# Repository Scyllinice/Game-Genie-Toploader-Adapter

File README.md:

# Game Genie Toploader Adapter

<p xmlns:cc="http://creativecommons.org/ns#" >This work by <span property="cc:attributionName">Scyllinice</span> is licensed under <a href="https://creativecommons.org/licenses/by-nc/4.0/?ref=chooser-v1" target="_blank" rel="license noopener noreferrer" style="display:inline-block;">Creative Commons Attribution-NonCommercial 4.0 International</a></p>

This is a adapter/riser PCB for using an original Game Genie on your top loading NES. It also works for clone NES systems that load directly from the cart instead of using emulation (a Retron 5, for example, will not work).

The only component needed to build this PCB into a functioning unit would be a 2.54mm pitch 2x36 pin (72 pin total) edge connector. You can search **5530843-8** for a part number as well.

I have had success using the following edge connectors:

* [Edge connector 1](https://www.aliexpress.us/item/3256802817047324.html)
* [Edge connector 2](https://www.aliexpress.us/item/2251832843397196.html)
* [DigiKey](https://www.digikey.com/en/products/detail/te-connectivity-amp-connectors/5530843-8/770547)

When soldering the edge connector to the top of the board, you will need to bend in the pins a bit as the board is only 1.2mm thick to match the original thickness of a NES retail cartridge. This helps preserve the NES cartridge connector. 

For longevity, it is recommended to use an ENIG finish with gold fingers. HASL (or Lead Free HASL) will still work, but it's more fragile and can fail over time.

[JLCPCB](https://jlcpcb.com/) is generally better priced for ENIG gold fingers than PCBWay. As the time of this writing, you can get 5 of these boards for about $20 US at JLCPCB.

## 3D printed enclosure — [`mech/`](mech/README.md)

A two-part shell, **106.1 × 16.8 × 58.4 mm**, held together by two M2 screws through
the board's own mounting holes. Prints without supports; `mech/front.stl` and
`mech/back.stl` are ready to slice.

## The KiCad project lives in [`pcb/`](pcb/README.md)

The board is now **generated from source rather than drawn**: a 72-pin pinout table and
a set of measured dimensions, from which the footprints, symbols, schematic, board,
copper and fab outputs are all produced by `make rebuild`.

```
cd pcb
make            check what is committed — DRC, ERC, card-edge rules, and the
                comparison against the board that was released
make rebuild    regenerate everything from the two source tables
make fab        gerbers, drill, position file, BOM
```

Regenerating wants the pinned toolchain — `./dc bash -c "cd pcb && make rebuild"` runs
it in a container with KiCad 10 and OpenSCAD, which is what the committed files were
built with. See [`.devcontainer/`](.devcontainer/README.md). Checking works with
whatever KiCad you have.

It is the same board. The hand-drawn files this project shipped with are frozen in
[`pcb/reference/`](pcb/reference/README.md), and every run subtracts the generated
board from them — 144 pads, 72 nets, 14 outline corners, both holes, all three silk
texts, to within 1 µm. Nothing about the physical board, the pinout or the fab package
has changed.

What the rebuild adds: a schematic that passes ERC (the drawn one reports 54 direction
conflicts, because one symbol was used for both ends of a pass-through), card-edge
checks KiCad's DRC does not have (finger pitch, front/back registration, the bevel
zone, the contact wipe path), ENIG and the 1.2 mm stackup declared in the gerber job
file rather than only in this README, and a rebuild that is byte-identical run to run.

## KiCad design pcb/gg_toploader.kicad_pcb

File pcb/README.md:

# pcb/ — the board

The Game Genie Toploader Adapter, generated from source instead of drawn. Two Python
tables describe the board — a 72-pin pinout and a set of measured dimensions — and
everything else here is produced from them: both footprints, both schematic symbols,
the schematic, the board, the copper, the project rules and the fab outputs.

**This is the project of record.** It replaced the hand-drawn files that used to sit
in the repository root, which are frozen in [`reference/`](reference/README.md) — not
as an archive, but because the check below reads them. The generated board is
subtracted from the released one on every run:

```
  PASS  outline  — 14 corners vs 14
  PASS  pad count  — 144 pads
  PASS  pad positions  — 144 pads within 0.001 mm
  PASS  pad sizes
  PASS  pad layers
  PASS  pad nets  — 72 nets
  PASS  net membership  — 72 nets
  PASS  1:1 pass-through  — 72/72 nets join J1 pin N to J2 pin N
  PASS  mounting holes  — (100.914, 79.451) d2.1, (171.348, 79.451) d2.1
  PASS  silk texts  — 3 texts

  The rebuild is geometrically and electrically identical to the released board.
```

## Running it

```
make            check what is here — DRC, ERC, card-edge rules, byte-canonical
                form, and the comparison above. Regenerates nothing.
make rebuild    the whole pipeline, pin table to routed board (FORCE=1 to overwrite
                a board that already carries routing)
make compare    just the equivalence proof
make fab        gerbers, drill, position file, BOM
make render     top and bottom PNGs, and the repository README's image
```

Needs KiCad 9 on the host — `kicad-cli` and the `pcbnew` Python module, both of which
Debian/Ubuntu's `kicad` package installs. No container. The generated files are KiCad
9 format while the released ones are KiCad 8, which is exactly why the comparison
loads both through pcbnew instead of diffing text.

## What the board is

A passive riser. 72 gold fingers go into a top-loading NES; a 2×36 2.54 mm card-edge
connector soldered to the top takes the Game Genie. Pin N to pin N, seventy-two times,
no components. The one and only complication:

**The two ends are on different pitches.** The console's cartridge slot is 2.50 mm and
the connector part is made in 2.54 mm, so every conductor has to shift sideways
between the two fields — 1.67 mm at one end of the board, 3.07 mm at the other. That
shift is the entire routing problem, and it is why the corridor between the two pad
fields is full of parallel diagonal jogs.

**Two mounting holes sit in that corridor** and four conductors cannot clear them in
either pad column, so they jog twice: once early, hold a safe X past the hole, then
finish the move in the 2.75 mm window between the hole and J1's pads. The released
board does this by hand. `route.py` derives it, and refuses to write a board where it
does not fit.

## The pipeline

```
lib/pinout.py      72 pins: nesdev name, this board's net label, symbol pin, direction
lib/geometry.py    the measured board: outline, both pad fields, holes, silk, rules
      |
      |  gen_footprints.py  -> lib/gg_adapter.pretty/   (2 footprints, 144 pads)
      |  gen_symbol.py      -> lib/gg_adapter.kicad_sym (2 symbols, mirrored)
      |  gen_schematic.py   -> gg_toploader.kicad_sch   (2 symbols, 144 labels)
      |  gen_board.py       -> gg_toploader.kicad_pcb   (placed + netted, unrouted)
      |  route.py           -> + 220 track segments, clearance-audited
      |  canonicalize.py    -> byte-reproducible (content-derived UUIDs, sorted items)
      |  gen_project.py     -> gg_toploader.kicad_pro + both lib tables
      v
   checks: kicad-cli drc (0/0) · kicad-cli erc (0) · check_fingers.py ·
           verify_rules.py · compare_original.py
```

`gen_project.py` runs **last**. `pcbnew.SaveBoard()` rewrites the sibling `.kicad_pro`
and resets the net classes to KiCad's stock defaults; `verify_rules.py` is what catches
it when that ordering slips.

## What the rebuild adds

Everything below is a difference from the released project, and each one is deliberate:

| | released | rebuild |
|---|---|---|
| ERC | 54 violations | **0** |
| symbols | one symbol used twice, all 72 nets output-to-output | two symbols, directions mirrored console↔Game Genie |
| symbol source | `doragasu:NES-CART`, a CERN-OHL-S library | generated from the nesdev wiki pin table |
| stackup finish | `None` | `ENIG` — reaches the fab in the gerber job file instead of living in a README |
| card-edge checks | none | pitch, registration, bevel zone, wipe path, mask, edge clearance |
| keepouts | none | rule areas over the bevel/wipe zone and the top edge |
| fab instructions | in this README | `fab/FABNOTES.txt`, in the zip with the gerbers |
| regeneration | n/a | byte-identical across runs |

DRC was already clean on the released board, and stays clean here: 0 violations,
0 unconnected.

## The card edge, and the check KiCad does not run

**DRC's copper-to-edge test does not look at pads.** Measured here: set
`min_copper_edge_clearance` to 5 mm — far enough that all 144 pads are inside it — and
the violation list comes back with 16 items, every one a *track*. Not one pad, at any
setting. On most boards that is a curiosity. On a card edge the pads are the thing
nearest the milled edge, so the check that matters is the one that does not run.

Two things cover it between them:

**Rule areas** (`gen_board.py`) over the bevel/wipe zone at the insertion edge and over
the top edge. Nothing may be *routed* into either band. The insertion-edge one is there
twice over: a 45° gold-finger bevel takes ~0.6 mm off the top surface, so copper inside
it is copper the mill cuts through — and the console's contacts sweep that same strip
on every insertion, so a track crossing it shorts to each contact as it passes. They
are rule areas, not copper: the gerbers are byte-identical with and without them,
verified.

**`check_fingers.py`** measures what a keepout cannot enforce, because keepouts permit
pads. It reports the closest pad to any edge — J1.36 at **0.372 mm** — and fails only
below 0.20 mm, the floor a fab can actually hold on a routed edge. All 72 J1 pads sit
inside this project's own 0.5 mm rule, at 0.468 mm from the top edge. That is
as-released and as-fabricated: the connector land has to be where the connector is.
Noted every run, not changed.

**The bevel itself is not board geometry** — it is a process the fab applies, and
there is no field in any gerber that asks for it. That instruction now ships as
`fab/FABNOTES.txt` inside the fab package rather than living in a README, because a
fab that is not told sends back square-edged contacts that chew the console connector.

## Things worth knowing about this board

* **1.2 mm, not 1.6 mm.** Cartridge thickness. The stackup declares 1.11 mm core plus
  copper and mask to reach it, and the gerber job carries the number.
* **The finger setback is 0.62 mm** and a 45° gold-finger bevel on a 1.2 mm board
  reaches about 0.6 mm. That is a **0.02 mm margin** — `check_fingers.py` prints it
  every run because it is the kind of number you want to have seen before ordering.
* **Pins 1 and 72 are both GND and are NOT joined here.** They are separate nets
  (`CPU-GND`, `CIC-GND`) and meet in the console. `pinout.py` asserts it stays that
  way; bridging them would be a change of circuit, not a cleanup.
* **PPU A11 and A10 really are swapped** at pins 62/63. Wiki and released board agree.
* **CIRAM A10 and CIRAM /CE are driven by the cartridge**, so they are the two signals
  whose direction runs Game-Genie-to-console. The released symbol has them as inputs;
  this is the only place the rebuild's pin table disagrees with it, and it changes
  nothing but ERC.

## Traps this cost, written down where they happened

* `.kicad_pcb` writes text size in the **opposite order** to `VECTOR2I`, and
  `SetBold()` **recomputes thickness**, so it has to be called before setting it.
  Between them, the long silk text came out short, fat and off the edge.
* A schematic's inlined `lib_symbols` copy is **library-qualified**, but its
  `_0_0`/`_1_1` sub-symbols are **not**. Get it wrong and KiCad rejects the whole file
  with "Failed to load schematic" and no line number.
* That inlined copy is compared **field by field** against the library. A description
  that differs by one word is an ERC warning, which is why both files build their
  symbols from one table.
* The escape columns beside a mounting hole are `hx ± R`, and `(hx - R) - hx` is not
  exactly `-R` in floating point, so an exact-fit candidate rejects itself. Two
  conductors failed to route over 1e-13 mm.

## Files

| file | what it makes |
|---|---|
| `lib/pinout.py` | the 72-pin table — run it to print the pinout |
| `lib/geometry.py` | measured geometry — run it to print the dimensions |
| `gen_footprints.py` | `lib/gg_adapter.pretty/` — the fingers and the connector land |
| `gen_symbol.py` | `lib/gg_adapter.kicad_sym` — two direction-mirrored symbols |
| `gen_schematic.py` | the schematic: two symbols, 144 labels, no wires |
| `gen_board.py` | the board: outline, placement, holes, silk, 72 nets |
| `route.py` | the copper, in closed form, clearance-audited before it is written |
| `canonicalize.py` | content-derived UUIDs so a no-op rebuild is a no-op diff |
| `gen_project.py` | net classes, design rules, both library tables |
| `gen_bom.py` | the BOM — one line, plus the fab notes that matter |
| `gen_render.py` | the two renders, and the repository README's image |
| `compare_original.py` | the equivalence proof against the released board |
| `check_fingers.py` | card-edge checks KiCad's DRC does not have |
| `verify_rules.py` | asserts `SaveBoard()` has not eaten the net classes |
| `guard_routed.py` | refuses to regenerate over routing |
| `reference/` | the released design, frozen — what `compare_original.py` reads |

## Changing the board

Edit the table, not the file. A pin's net name lives in `lib/pinout.py`; a dimension
lives in `lib/geometry.py`; where the copper goes is a rule in `route.py`. Then
`make rebuild`, and read the diff — it will be small, because the board is
canonicalised.

Opening `gg_toploader.kicad_pcb` in KiCad and dragging something works, and the next
`make rebuild` discards it. That is not a warning against using the GUI: it is the
fastest way to try a change. Try it there, then fold the numbers back into the table
that owns them.

One consequence of the promotion is worth stating plainly: **`make compare` is now a
regression test, not a migration check.** It answers "does the board still match what
was fabricated and sold", so a deliberate design change is supposed to break it. When
that happens, the fix is to read exactly which of the fourteen lines changed, satisfy
yourself that it is the change you meant, and say so in the commit — not to relax the
check. `reference/` never moves.

`production/` in the repository root is the fab package the released board was ordered
from. It has not been regenerated: it corresponds to the design this board is proven
identical to, and `make fab` produces its replacement when there is a reason to order
again.

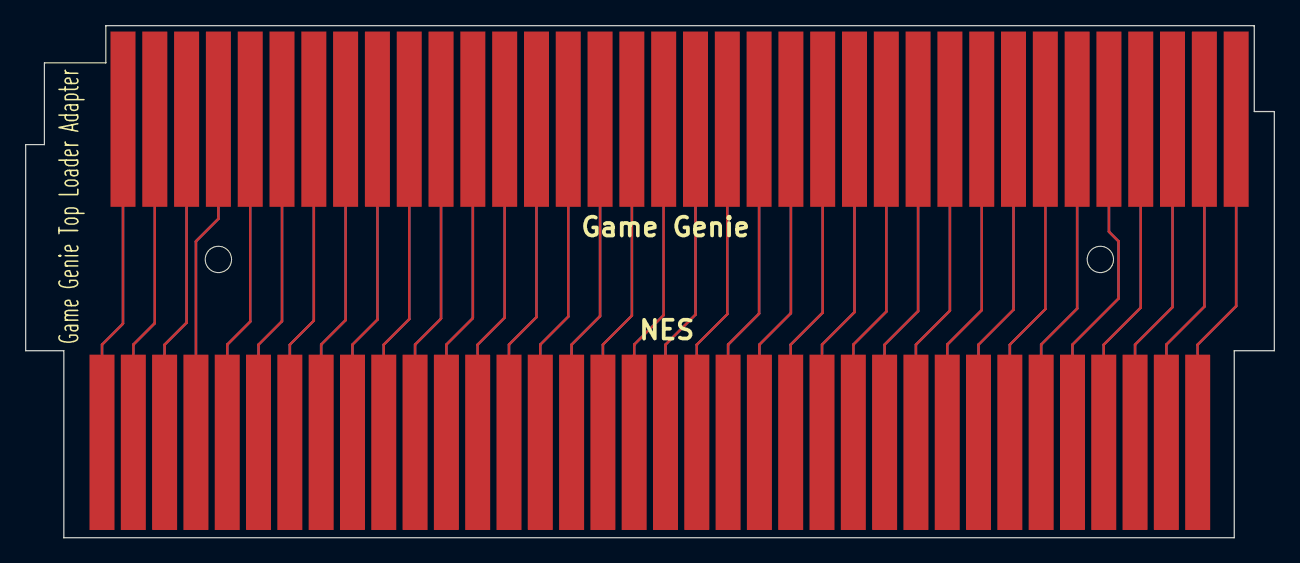
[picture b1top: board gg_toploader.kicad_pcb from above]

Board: 2 copper layers, 99.7 x 40.9 mm, 4 parts (0 on the bottom side), 72 nets.

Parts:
J1: 5530843-8; GG_2x36_2.54mm_Edge
J2: NES_CART_FINGERS
MOUNT1, MOUNT2: MountingHole_2.1mm

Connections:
/4MHz: J1.71, J2.71
/21.48MHz: J1.37, J2.37
/CIC-GND: J1.72, J2.72
/CIC-VCC: J1.36, J2.36
/CPU-A0: J1.13, J2.13
/CPU-A1: J1.12, J2.12
/CPU-A2: J1.11, J2.11
/CPU-A3: J1.10, J2.10
/CPU-A4: J1.9, J2.9
/CPU-A5: J1.8, J2.8
/CPU-A6: J1.7, J2.7
/CPU-A7: J1.6, J2.6
/CPU-A8: J1.5, J2.5
/CPU-A9: J1.4, J2.4
/CPU-A10: J1.3, J2.3
/CPU-A11: J1.2, J2.2
/CPU-A12: J1.39, J2.39
/CPU-A13: J1.40, J2.40
/CPU-A14: J1.41, J2.41
/CPU-D0: J1.49, J2.49
/CPU-D1: J1.48, J2.48
/CPU-D2: J1.47, J2.47
/CPU-D3: J1.46, J2.46
/CPU-D4: J1.45, J2.45
/CPU-D5: J1.44, J2.44
/CPU-D6: J1.43, J2.43
/CPU-D7: J1.42, J2.42
/CPU-GND: J1.1, J2.1
/CPU-R/~W: J1.14, J2.14
/CPU-~IRQ: J1.15, J2.15
/CPU-~PRG: J1.50, J2.50
/EXP0: J1.16, J2.16
/EXP1: J1.17, J2.17
/EXP2: J1.18, J2.18
/EXP3: J1.19, J2.19
/EXP4: J1.20, J2.20
/EXP5: J1.55, J2.55
/EXP6: J1.54, J2.54
/EXP7: J1.53, J2.53
/EXP8: J1.52, J2.52
/EXP9: J1.51, J2.51
/PHI2: J1.38, J2.38
/PPU-A0: J1.29, J2.29
/PPU-A1: J1.28, J2.28
/PPU-A2: J1.27, J2.27
/PPU-A3: J1.26, J2.26
/PPU-A4: J1.25, J2.25
/PPU-A5: J1.24, J2.24
/PPU-A6: J1.23, J2.23
/PPU-A7: J1.59, J2.59
/PPU-A8: J1.60, J2.60
/PPU-A9: J1.61, J2.61
/PPU-A10: J1.63, J2.63
/PPU-A11: J1.62, J2.62
/PPU-A12: J1.64, J2.64
/PPU-A13: J1.65, J2.65
/PPU-D0: J1.30, J2.30
/PPU-D1: J1.31, J2.31
/PPU-D2: J1.32, J2.32
/PPU-D3: J1.33, J2.33
/PPU-D4: J1.69, J2.69
/PPU-D5: J1.68, J2.68
/PPU-D6: J1.67, J2.67
/PPU-D7: J1.66, J2.66
/PPU-VA10: J1.22, J2.22
/PPU-~A13: J1.58, J2.58
/PPU-~R: J1.21, J2.21
/PPU-~VCS: J1.57, J2.57
/PPU-~W: J1.56, J2.56
/S0: J1.34, J2.34
/S1: J1.35, J2.35
/S2: J1.70, J2.70

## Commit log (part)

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2024-05-11 Commit KiCAD files
2024-05-11 Add License
2024-05-11 Add Digi-Key link and part number
2024-05-11 Add image
2024-05-11 Add note about JLCPCB
